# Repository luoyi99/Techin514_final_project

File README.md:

# Techin514_final_project
## Part 1
### Jumping Jacks Counter
 A basic fitness tracker that monitors and displays key metrics like the number of jumps, rate (jumps per minute), heart rate and calories burned. The project integrates an accelerometer for motion sensing, a pulse sensor for heart rate monitoring, a display mechanism using screen and stepper motor-driven gauge needle, and a button for reset.

## Part 2 - Sensor Device
The sensor device will include a MPU6050 motion sensor, a pulse sensor, a ESP32S3 processor and a battery. The components will be sewed on a glove so users can wear it when doing jumping jacks without worrying it to fall down.

## Part 3 - Display Device
The display device will include a ESP32S3 processor, a battery, a OLED screen, a button, a LED, a stepper motor driver breakout board (Adafruit TB6612 1.2A DC/Stepper Motor Driver Breakout Board) and a stepper-motor-driven gauge needle (x27.168). 

## Part 4

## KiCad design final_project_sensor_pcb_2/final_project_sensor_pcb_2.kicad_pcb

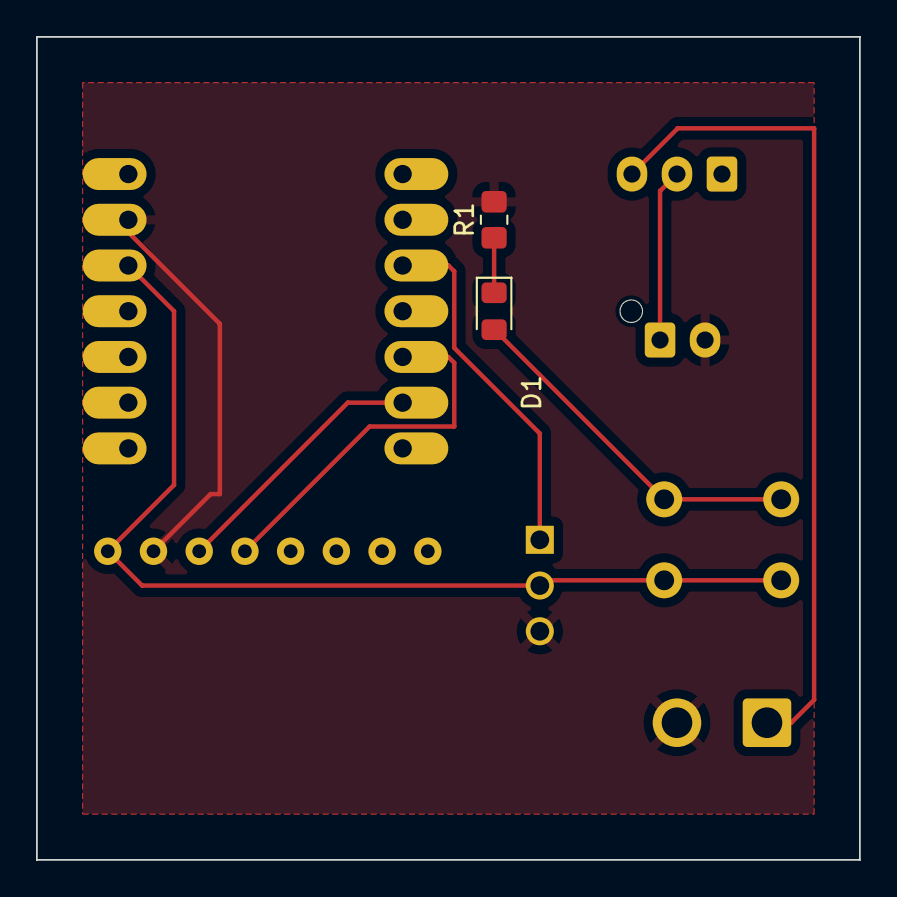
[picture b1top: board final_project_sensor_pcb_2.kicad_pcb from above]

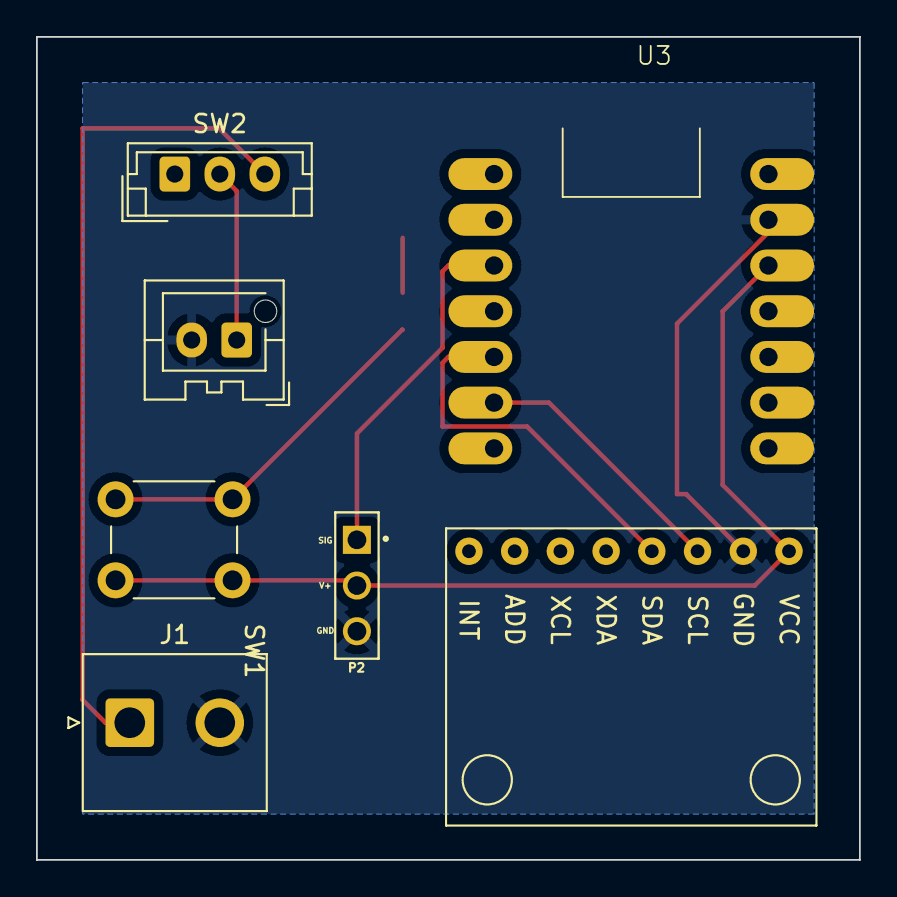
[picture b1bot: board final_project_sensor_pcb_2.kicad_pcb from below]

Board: 2 copper layers, 45.7 x 45.7 mm, 9 parts (7 on the bottom side), 8 nets.

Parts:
BT1: Battery_Cell; JST_XA_B02B-XASK-1-A_1x02_P2.50mm_Vertical
D1: LED; LED_0805_2012Metric_Pad1.15x1.40mm_HandSolder
J1: Conn_01x02_Pin; JST_NV_B02P-NV_1x02_P5.00mm_Vertical
P2: SEN-11574; XDCR_SEN-11574
R1: 1k; R_0805_2012Metric_Pad1.20x1.40mm_HandSolder
SW1: SW_SPST; SW_PUSH_6mm
SW2: SW_SPDT; JST_EH_B3B-EH-A_1x03_P2.50mm_Vertical
U1: module_mpu6050
U3: XIAO_ESP32_SENSE

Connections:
+3V3: P2.2 (V+), SW1.1 (A), U1.1 (VCC), U3.4 (GPIO4_A3_D3), U3.10 (3V3)
GND: BT1.2 (-), J1.2, P2.3 (GND), R1.2, U1.2 (GND), U3.9 (GND)
unnamed: BT1.1 (+), SW2.2 (B)
unnamed: D1.2 (A), SW1.2 (B)
unnamed: D1.1 (K), R1.1
unnamed: J1.1, SW2.3 (C)
unnamed: U1.3 (SCL), U3.6 (GPIO6_A5_D5_SCL)
unnamed: U1.4 (SDA), U3.5 (GPIO4_A3_D3_SDA)

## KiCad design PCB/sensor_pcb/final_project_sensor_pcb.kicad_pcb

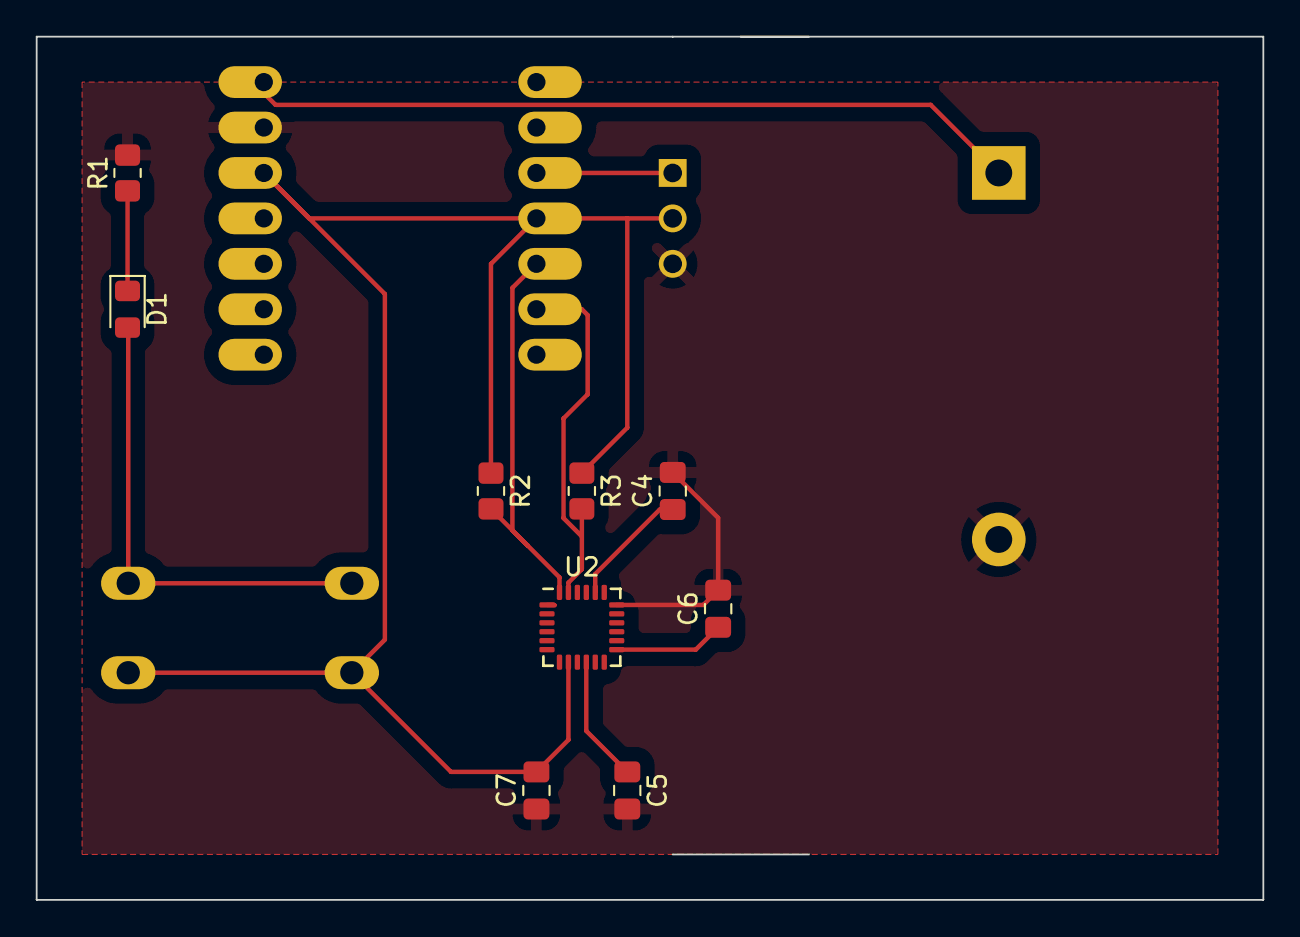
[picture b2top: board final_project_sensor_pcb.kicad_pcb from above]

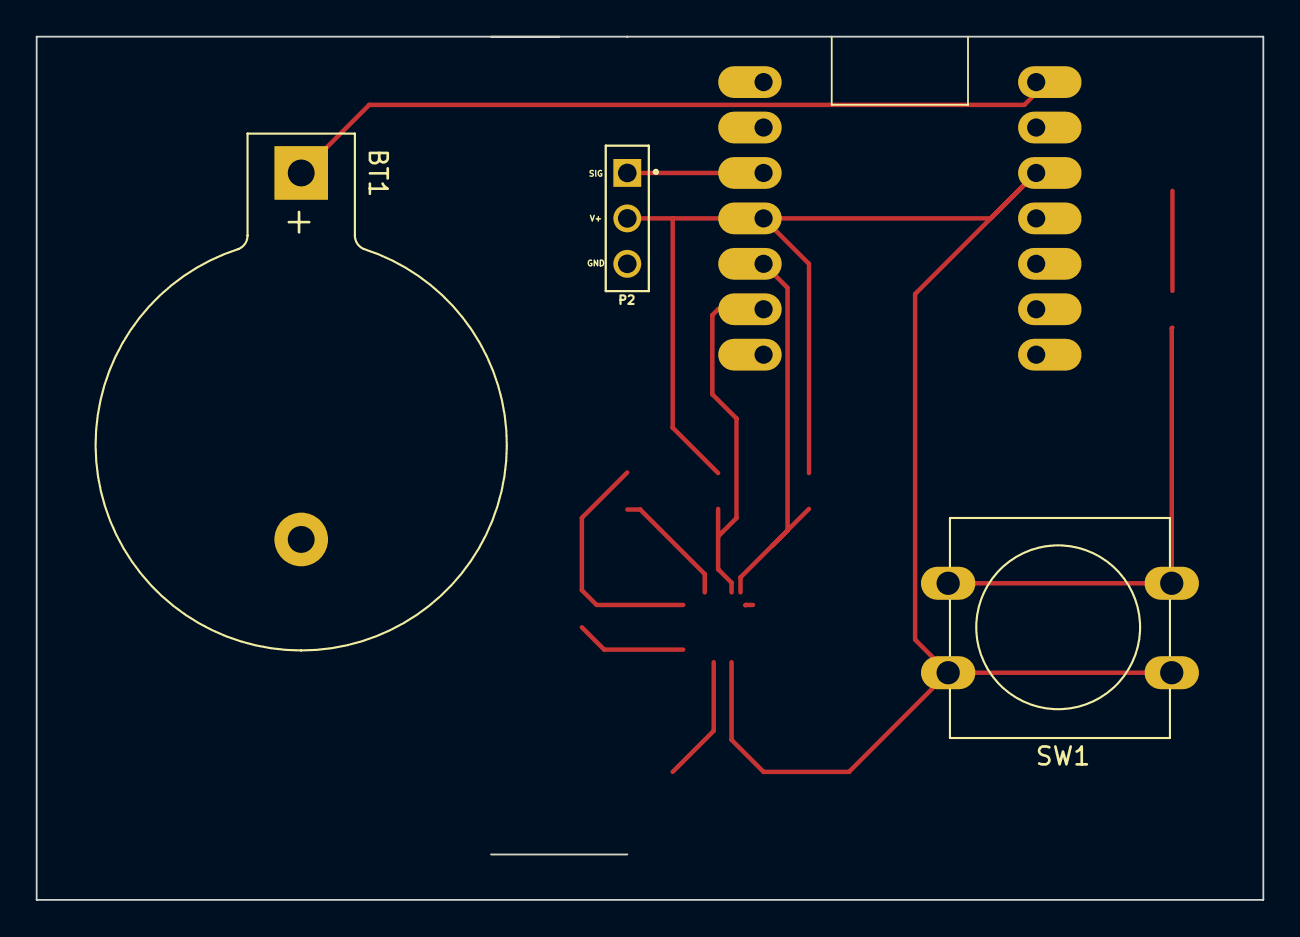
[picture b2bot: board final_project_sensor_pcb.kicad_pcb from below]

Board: 2 copper layers, 68.6 x 48.3 mm, 13 parts (4 on the bottom side), 9 nets.

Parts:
BT1: Battery_Cell; BatteryHolder_Keystone_103_1x20mm
C4: 220pf; C_0805_2012Metric_Pad1.18x1.45mm_HandSolder
C5, C6, C7: 0.1uf; C_0805_2012Metric_Pad1.18x1.45mm_HandSolder
D1: LED; LED_0805_2012Metric_Pad1.15x1.40mm_HandSolder
P2: SEN-11574; XDCR_SEN-11574
R1: 1k; R_0805_2012Metric_Pad1.20x1.40mm_HandSolder
R2, R3: 4.7k; R_0805_2012Metric_Pad1.20x1.40mm_HandSolder
SW1: SW_SPST; SW_PUSH-12mm
U1: XIAO_ESP32_SENSE
U2: MPU-6050; InvenSense_QFN-24_4x4mm_P0.5mm

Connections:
+3V3: C6.1, C7.2, P2.2 (V+), R2.1, R3.1, SW1.1 (A), U1.4 (GPIO4_A3_D3), U1.10 (3V3), U2.8 (VLOGIC), U2.13 (VDD)
/BAT: BT1.1 (+), U1.8 (5V)
GND: BT1.2 (-), C4.2, C5.2, C6.2, C7.1, P2.3 (GND), R1.2, U1.9 (GND), U2.1 (CLKIN), U2.11 (FSYNC), U2.18 (GND)
unnamed: D1.2 (A), SW1.2 (B)
unnamed: D1.1 (K), R1.1
unnamed: R2.2, U1.5 (GPIO4_A3_D3_SDA), U2.24 (SDA)
unnamed: R3.2, U1.6 (GPIO6_A5_D5_SCL), U2.23 (SCL)
unnamed: C4.1, U2.20 (CPOUT)
unnamed: C5.1, U2.10 (REGOUT)

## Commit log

2024-01-17 added datasheets and README.md
2024-01-17 updated images in README.md and datasheet files
2024-01-18 added PCB schematic diagrams
2024-01-18 edited pictures in README.md
2024-02-07 lab5_power_estimate
2024-03-04 everything
2024-03-05 final
